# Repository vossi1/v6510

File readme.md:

# V6510 - Replacement for a 6510 with a 6502  

**Copyright (c) 2024 Vossi - v.3**

**www.mos6502.net**

## License
This work is licensed under a Creative Commons Attribution-ShareAlike 4.0
International License. See [https://creativecommons.org/licenses/by-sa/4.0/](https://creativecommons.org/licenses/by-sa/4.0/).

:thumbsup: v.3 now without PHI2 selection, because the v6510 only works with buffered PHI2! :wink:

**[Schematic](https://github.com/vossi1/v6510/blob/master/v6510_v3.png)**

**[Parts](https://github.com/vossi1/v6510/blob/master/parts.txt)**

**CPLD-Firmware:** The .JED file can be uploaded with a JTAG-SMT2 Xilinx programmer (China) and [xc3sprog](https://xc3sprog.sourceforge.net/)

:exclamation: **BEWARE: I got good CPLD's from China, but there are some XC9572XL FAKES out there!**

I just got these 10ns cplds and they don't work - but I don't think 7ns is really necessary: 

V6510 in my 250407 test-board:

**For a WDC 65C02 you have to cut the small trace in the other solder jumper.**

Bottom view with Xilinx CPLD:

:white_check_mark: **Tested successfully in a 250407 board with:**

Cartridges:
REU1764 (Demo, Sonic), Magic Voice, IEEE-Interface, Sound Sampler, 
Formel 64, Final Cartridge 3, Dead Test, Diagnostic Test, 
Wizard of War / Gorf / ABeeCee with speech, 
Donkey Kong, Choplifter, Le Mans, Wizard of War Ultimax, Mini Basic, 
Magic Desk, Archon-Cart

Devices:
1541, 1581, Mouse 1351, Paddles, Joysticks, SwinSid Nano, Merlin PP64 (Promenade)

Software:
Geos 1.2, Geos 2.5, Super Mario, Last Ninja, Giana Sisters

:x: **Not working**

ROOS 80 Zeichenkarte = Zero 80 (Runs sometimes with a mos6502 CPU)

**Tested boards**

PAL: 250407 Rev. B, 250469 Rev. 4, KU-14194HB

**Tested CPU's**

mos 6502, mos 6502AD, mos 6502B, UM6502A, SY6502, R6502P

CMOS not working with REU, Magic Voice, ???: GTEµ G65SC02P-2, CMD G65SC02PI-2

My test-CPU's:

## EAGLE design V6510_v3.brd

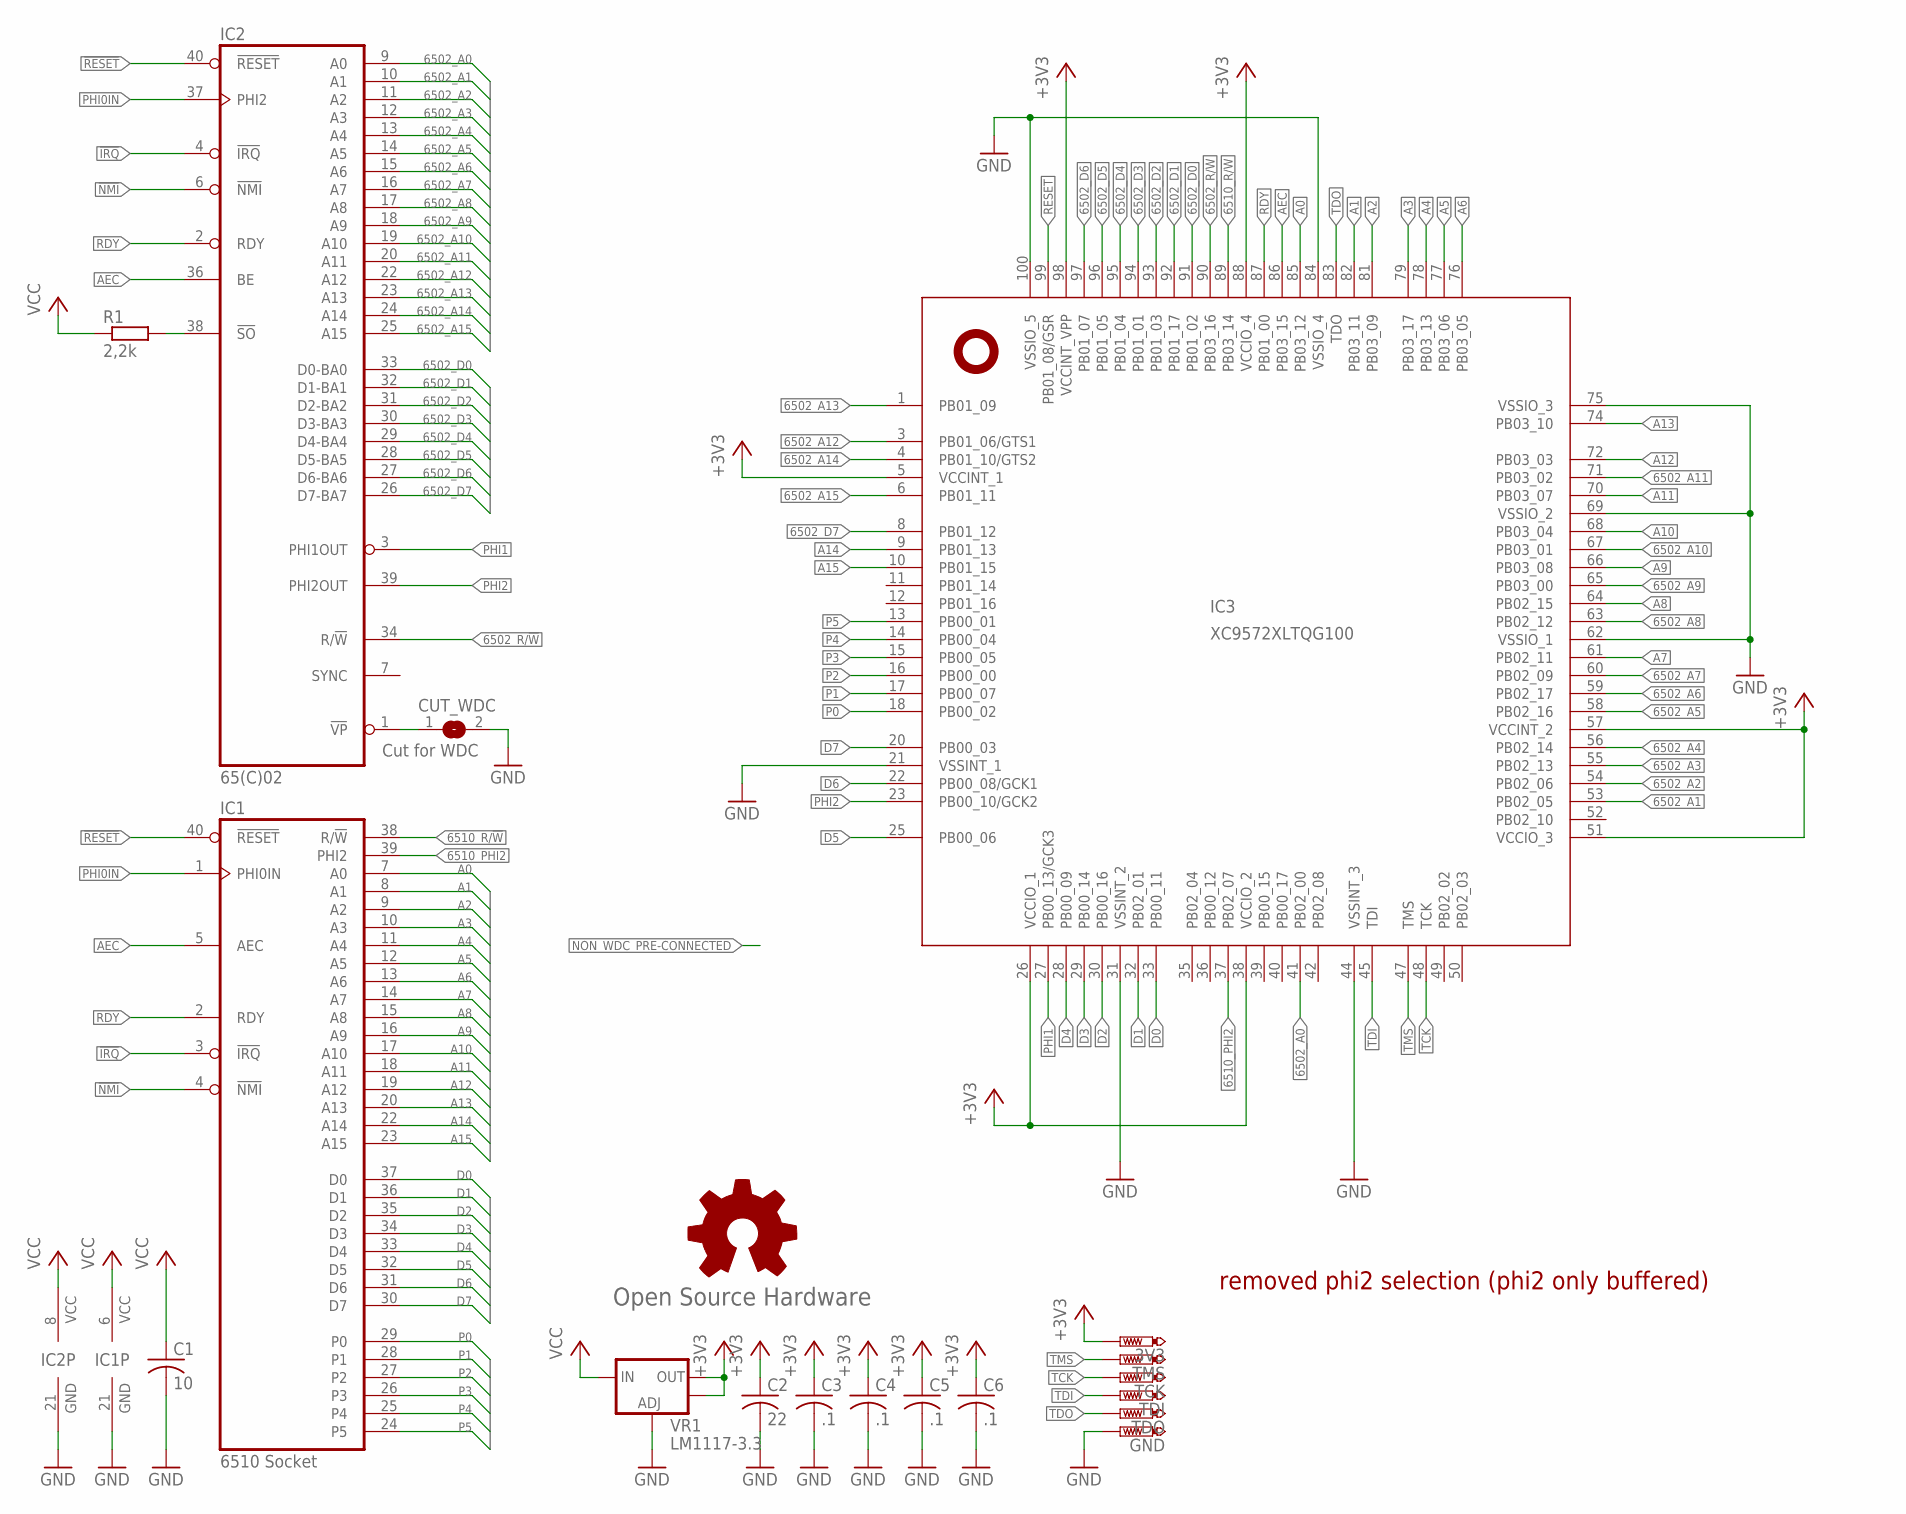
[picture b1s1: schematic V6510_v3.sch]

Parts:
3V3: PTR1TP08R; TP08R
C1: 10; C0805
C2: 22; C0805
C3, C4, C5, C6: .1; C0603
CUT_WDC: Cut for WDC; SJ
GND: PTR1TP08R; TP08R
GOLD_ORB_SM1: Open Source Hardware; OSHW_5MM
IC1: 6510 Socket; DIL40-ROUNDPAD
IC2: 65(C)02; DIL40-ROUNDPAD
IC3: XC9572XLTQG100; TQFP100
R1: 2,2k; 0603
TCK: PTR1TP08R; TP08R
TDI: PTR1TP08R; TP08R
TDO: PTR1TP08R; TP08R
TMS: PTR1TP08R; TP08R
VR1: LM1117-3.3; SOT223

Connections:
6502_A0: IC2.9 (A0), IC3.41 (PB02_00)
6502_A1: IC2.10 (A1), IC3.53 (PB02_05)
6502_A2: IC2.11 (A2), IC3.54 (PB02_06)
6502_A3: IC2.12 (A3), IC3.55 (PB02_13)
6502_A4: IC2.13 (A4), IC3.56 (PB02_14)
6502_A5: IC2.14 (A5), IC3.58 (PB02_16)
6502_A6: IC2.15 (A6), IC3.59 (PB02_17)
6502_A7: IC2.16 (A7), IC3.60 (PB02_09)
6502_A8: IC2.17 (A8), IC3.63 (PB02_12)
6502_A9: IC2.18 (A9), IC3.65 (PB03_00)
6502_A10: IC2.19 (A10), IC3.67 (PB03_01)
6502_A11: IC2.20 (A11), IC3.71 (PB03_02)
6502_A12: IC2.22 (A12), IC3.3 (PB01_06/GTS1)
6502_A13: IC2.23 (A13), IC3.1 (PB01_09)
6502_A14: IC2.24 (A14), IC3.4 (PB01_10/GTS2)
6502_A15: IC2.25 (A15), IC3.6 (PB01_11)
6502_D0: IC2.33 (D0-BA0), IC3.91 (PB01_02)
6502_D1: IC2.32 (D1-BA1), IC3.92 (PB01_17)
6502_D2: IC2.31 (D2-BA2), IC3.93 (PB01_03)
6502_D3: IC2.30 (D3-BA3), IC3.94 (PB01_01)
6502_D4: IC2.29 (D4-BA4), IC3.95 (PB01_04)
6502_D5: IC2.28 (D5-BA5), IC3.96 (PB01_05)
6502_D6: IC2.27 (D6-BA6), IC3.97 (PB01_07)
6502_D7: IC2.26 (D7-BA7), IC3.8 (PB01_12)
6502_R/!W: IC2.34 (R/!W), IC3.90 (PB03_16)
6502_VSS: CUT_WDC.1, IC2.1 (!VP)
6510_PHI2: IC1.39 (PHI2), IC3.37 (PB02_07)
6510_R/!W: IC1.38 (R/!W), IC3.89 (PB03_14)
!IRQ: IC1.3 (!IRQ), IC2.4 (!IRQ)
!NMI: IC1.4 (!NMI), IC2.6 (!NMI)
!RESET: IC1.40 (!RESET), IC2.40 (!RESET), IC3.99 (PB01_08/GSR)
!SO: IC2.38 (!SO), R1.2
+3V3: 3V3.TP, C2.1, C3.1, C4.1, C5.1, C6.1, IC3.5 (VCCINT_1), IC3.26 (VCCIO_1), IC3.38 (VCCIO_2), IC3.51 (VCCIO_3), IC3.57 (VCCINT_2), IC3.88 (VCCIO_4), IC3.98 (VCCINT_VPP), VR1.2 (OUT), VR1.4 (OUT)
A0: IC1.7 (A0), IC3.85 (PB03_12)
A1: IC1.8 (A1), IC3.82 (PB03_11)
A2: IC1.9 (A2), IC3.81 (PB03_09)
A3: IC1.10 (A3), IC3.79 (PB03_17)
A4: IC1.11 (A4), IC3.78 (PB03_13)
A5: IC1.12 (A5), IC3.77 (PB03_06)
A6: IC1.13 (A6), IC3.76 (PB03_05)
A7: IC1.14 (A7), IC3.61 (PB02_11)
A8: IC1.15 (A8), IC3.64 (PB02_15)
A9: IC1.16 (A9), IC3.66 (PB03_08)
A10: IC1.17 (A10), IC3.68 (PB03_04)
A11: IC1.18 (A11), IC3.70 (PB03_07)
A12: IC1.19 (A12), IC3.72 (PB03_03)
A13: IC1.20 (A13), IC3.74 (PB03_10)
A14: IC1.22 (A14), IC3.9 (PB01_13)
A15: IC1.23 (A15), IC3.10 (PB01_15)
AEC: IC1.5 (AEC), IC2.36 (BE), IC3.86 (PB03_15)
D0: IC1.37 (D0), IC3.33 (PB00_11)
D1: IC1.36 (D1), IC3.32 (PB02_01)
D2: IC1.35 (D2), IC3.30 (PB00_16)
D3: IC1.34 (D3), IC3.29 (PB00_14)
D4: IC1.33 (D4), IC3.28 (PB00_09)
D5: IC1.32 (D5), IC3.25 (PB00_06)
D6: IC1.31 (D6), IC3.22 (PB00_08/GCK1)
D7: IC1.30 (D7), IC3.20 (PB00_03)
GND: C1.2, C2.2, C3.2, C4.2, C5.2, C6.2, CUT_WDC.2, GND.TP, IC1.21 (GND), IC2.21 (GND), IC3.21 (VSSINT_1), IC3.31 (VSSINT_2), IC3.44 (VSSINT_3), IC3.62 (VSSIO_1), IC3.69 (VSSIO_2), IC3.75 (VSSIO_3), IC3.84 (VSSIO_4), IC3.100 (VSSIO_5), VR1.1 (ADJ)
P0: IC1.29 (P0), IC3.18 (PB00_02)
P1: IC1.28 (P1), IC3.17 (PB00_07)
P2: IC1.27 (P2), IC3.16 (PB00_00)
P3: IC1.26 (P3), IC3.15 (PB00_05)
P4: IC1.25 (P4), IC3.14 (PB00_04)
P5: IC1.24 (P5), IC3.13 (PB00_01)
PHI0IN: IC1.1 (PHI0IN), IC2.37 (PHI2)
PHI1: IC2.3 (PHI1OUT), IC3.27 (PB00_13/GCK3)
PHI2: IC2.39 (PHI2OUT), IC3.23 (PB00_10/GCK2)
RDY: IC1.2 (RDY), IC2.2 (RDY), IC3.87 (PB01_00)
TCK: IC3.48 (TCK), TCK.TP
TDI: IC3.45 (TDI), TDI.TP
TDO: IC3.83 (TDO), TDO.TP
TMS: IC3.47 (TMS), TMS.TP
VCC: C1.1, IC1.6 (VCC), IC2.8 (VCC), R1.1, VR1.3 (IN)

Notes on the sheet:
removed phi2 selection (phi2 only buffered)

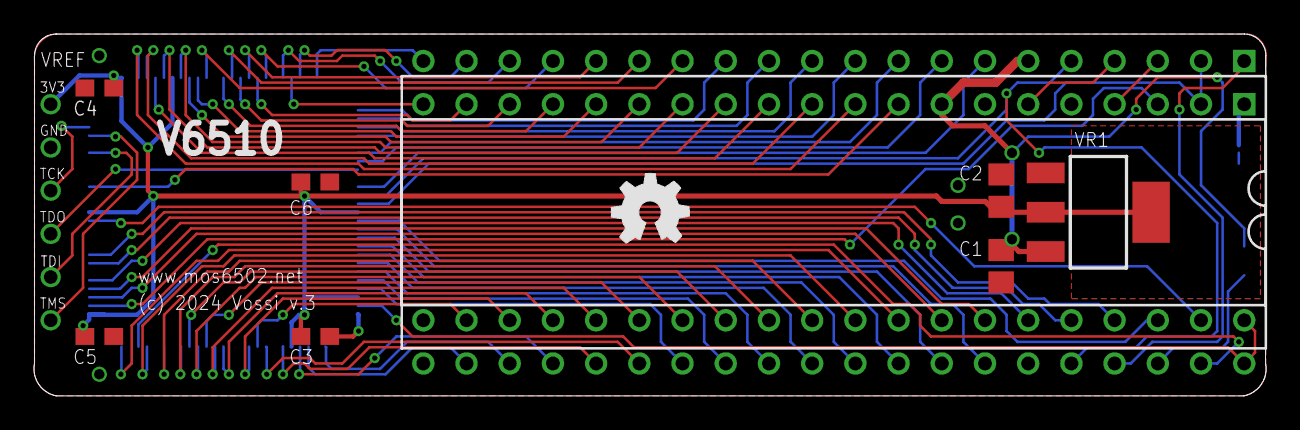
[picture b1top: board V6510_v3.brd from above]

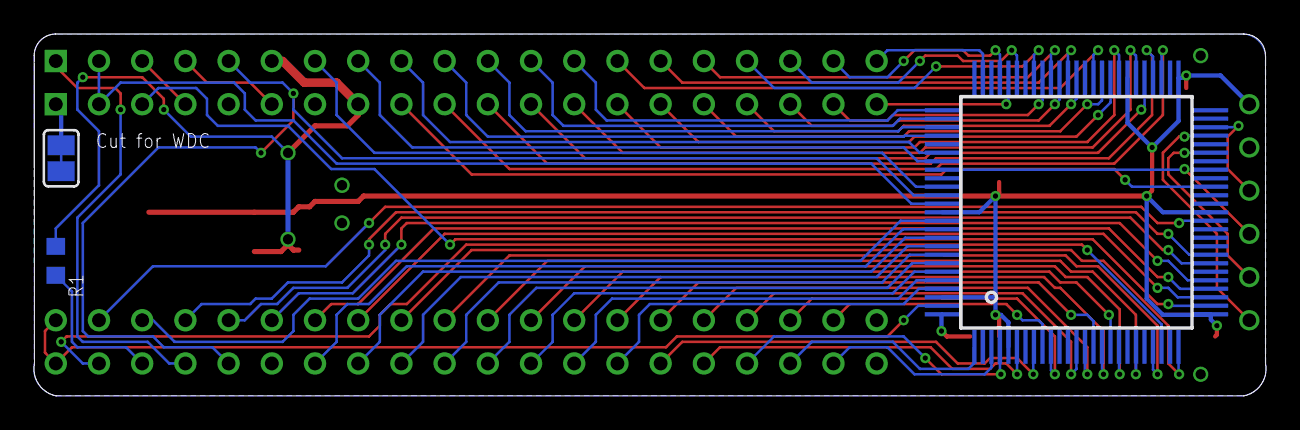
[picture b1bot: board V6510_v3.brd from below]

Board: 2 copper layers, 72.4 x 21.3 mm, 19 parts (3 on the bottom side), 74 nets.

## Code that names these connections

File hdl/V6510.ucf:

#NET "rdy"  LOC = "P87"  ; 

#PACE: Start of Constraints generated by PACE

#PACE: Start of PACE I/O Pin Assignments
NET "_reset"  LOC = "P99"  ; 
NET "address_6502<0>"  LOC = "P41"  ; 
NET "address_6502<10>"  LOC = "P67"  ; 
NET "address_6502<11>"  LOC = "P71"  ; 
NET "address_6502<12>"  LOC = "P3"  ; 
NET "address_6502<13>"  LOC = "P1"  ; 
NET "address_6502<14>"  LOC = "P4"  ; 
NET "address_6502<15>"  LOC = "P6"  ; 
NET "address_6502<1>"  LOC = "P53"  ; 
NET "address_6502<2>"  LOC = "P54"  ; 
NET "address_6502<3>"  LOC = "P55"  ; 
NET "address_6502<4>"  LOC = "P56"  ; 
NET "address_6502<5>"  LOC = "P58"  ; 
NET "address_6502<6>"  LOC = "P59"  ; 
NET "address_6502<7>"  LOC = "P60"  ; 
NET "address_6502<8>"  LOC = "P63"  ; 
NET "address_6502<9>"  LOC = "P65"  ; 
NET "address_6510<0>"  LOC = "P85"  ; 
NET "address_6510<10>"  LOC = "P68"  ; 
NET "address_6510<11>"  LOC = "P70"  ; 
NET "address_6510<12>"  LOC = "P72"  ; 
NET "address_6510<13>"  LOC = "P74"  ; 
NET "address_6510<14>"  LOC = "P9"  ; 
NET "address_6510<15>"  LOC = "P10"  ; 
NET "address_6510<1>"  LOC = "P82"  ; 
NET "address_6510<2>"  LOC = "P81"  ; 
NET "address_6510<3>"  LOC = "P79"  ; 
NET "address_6510<4>"  LOC = "P78"  ; 
NET "address_6510<5>"  LOC = "P77"  ; 
NET "address_6510<6>"  LOC = "P76"  ; 
NET "address_6510<7>"  LOC = "P61"  ; 
NET "address_6510<8>"  LOC = "P64"  ; 
NET "address_6510<9>"  LOC = "P66"  ; 
NET "aec"  LOC = "P86"  ; 
NET "data_6502<0>"  LOC = "P91"  ; 
NET "data_6502<1>"  LOC = "P92"  ; 
NET "data_6502<2>"  LOC = "P93"  ; 
NET "data_6502<3>"  LOC = "P94"  ; 
NET "data_6502<4>"  LOC = "P95"  ; 
NET "data_6502<5>"  LOC = "P96"  ; 
NET "data_6502<6>"  LOC = "P97"  ; 
NET "data_6502<7>"  LOC = "P8"  ; 
NET "data_6510<0>"  LOC = "P33"  ;
NET "data_6510<1>"  LOC = "P32"  ; 
NET "data_6510<2>"  LOC = "P30"  ;
NET "data_6510<3>"  LOC = "P29"  ;
NET "data_6510<4>"  LOC = "P28"  ;
NET "data_6510<5>"  LOC = "P25"  ;
NET "data_6510<6>"  LOC = "P22"  ;
NET "data_6510<7>"  LOC = "P20"  ;
NET "ioport<0>"  LOC = "P18"  ;
NET "ioport<1>"  LOC = "P17"  ;
NET "ioport<2>"  LOC = "P16"  ;
NET "ioport<3>"  LOC = "P15"  ;
NET "ioport<4>"  LOC = "P14"  ;
NET "ioport<5>"  LOC = "P13"  ;
NET "phi1"  LOC = "P27"  ; 
NET "phi2"  LOC = "P23"  ; 
NET "phi2_cpld"  LOC = "P37"  ; 
NET "r_w_6502"  LOC = "P90"  ; 
NET "r_w_6510"  LOC = "P89"  ; 

#PACE: Start of PACE Area Constraints

#PACE: Start of PACE Prohibit Constraints

#PACE: End of Constraints generated by PACE

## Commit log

2024-03-09 initial v2
2024-03-09 solder jumper desc
2024-03-09 partslist
2024-03-09 solder buffered phi2
2024-03-09 roos 80 zeichenkarte not working
2024-03-10 updated cpld order code
2024-03-10 test parts updated
2024-03-10 archon-cart
2024-03-13 Giana
2024-04-03 typo
2024-04-06 v3 phi2 only buffered
2024-04-06 reuploaded gerber v2 because v3 is not tested
2024-04-19 v3 tested
2024-04-23 cplds not good photo
2024-06-07 removed jlcjljlc
2024-06-20 license cc4
2025-01-10 added eagle files
2025-01-10 added firmware programming doc

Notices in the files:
parts and their libraries:
SparkFun: Licensing: CC v3.0 Share-Alike You are welcome to use this library for commercial purposes.
